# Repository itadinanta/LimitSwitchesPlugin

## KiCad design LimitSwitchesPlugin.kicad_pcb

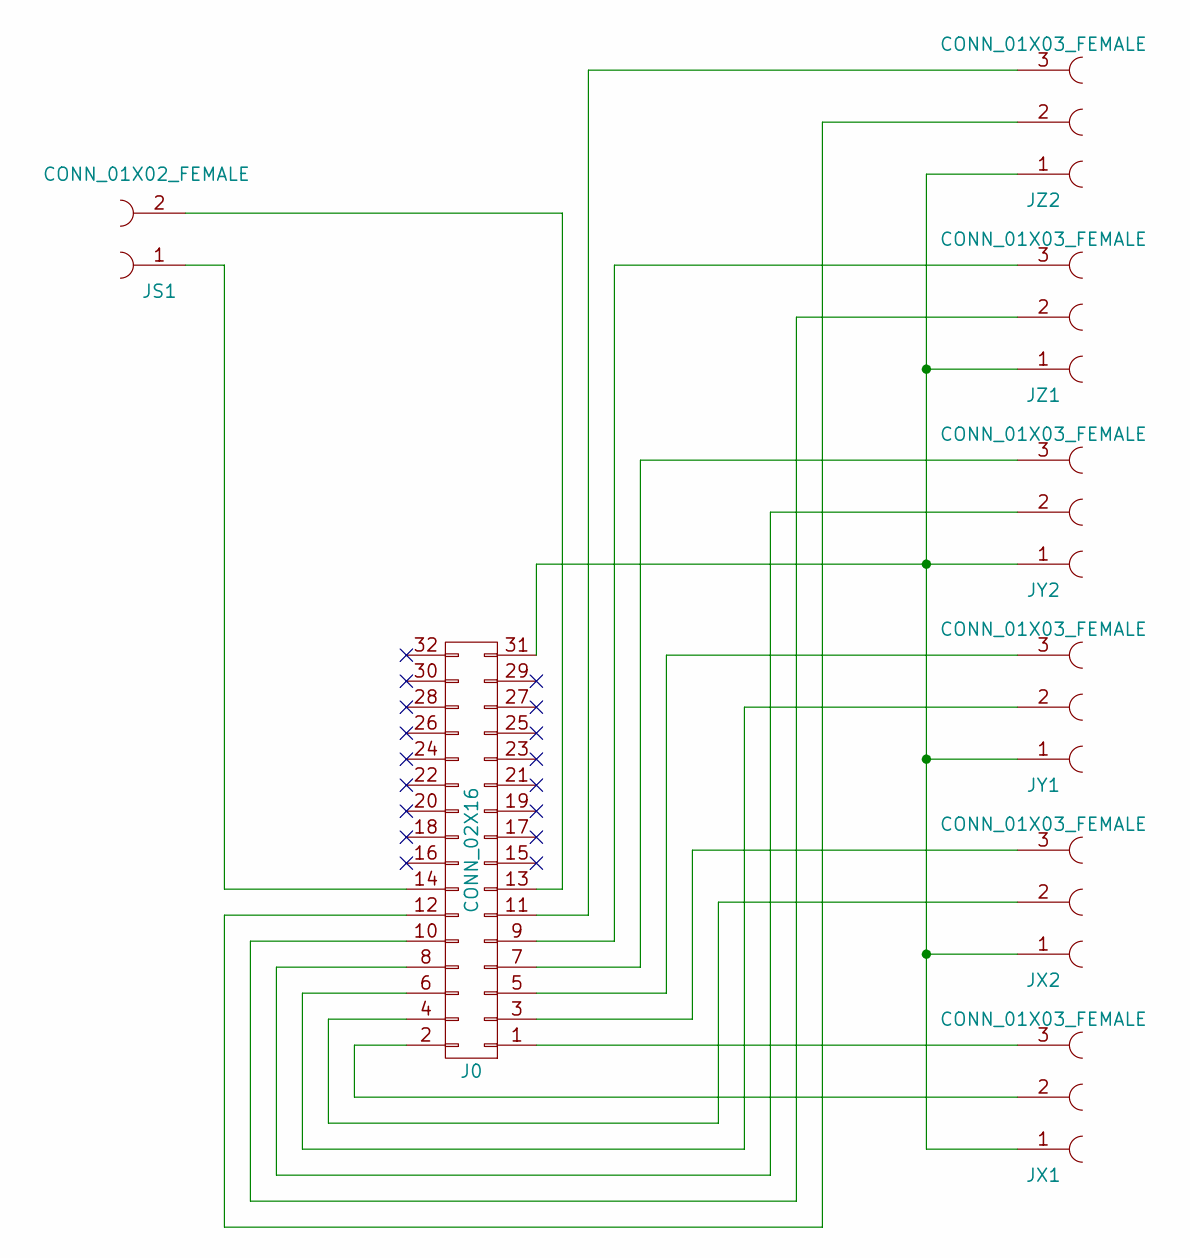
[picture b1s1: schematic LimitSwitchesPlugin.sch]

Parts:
J0: CONN_02X16; Pin_Header_Straight_2x16_Pitch2.54mm
JS1: CONN_01X02_FEMALE; JST_XH_B02B-XH-A_02x2.50mm_Straight
JX1, JX2: CONN_01X03_FEMALE; JST_XH_B03B-XH-A_03x2.50mm_Straight
JY1, JY2: CONN_01X03_FEMALE; JST_XH_B03B-XH-A_03x2.50mm_Straight
JZ1, JZ2: CONN_01X03_FEMALE; JST_XH_B03B-XH-A_03x2.50mm_Straight

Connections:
unnamed: J0.1, JX1.3
unnamed: J0.2, JX1.2
unnamed: J0.3, JX2.3
unnamed: J0.4, JX2.2
unnamed: J0.5, JY1.3
unnamed: J0.6, JY1.2
unnamed: J0.7, JY2.3
unnamed: J0.8, JY2.2
unnamed: J0.9, JZ1.3
unnamed: J0.10, JZ1.2
unnamed: J0.11, JZ2.3
unnamed: J0.12, JZ2.2
unnamed: J0.13, JS1.2
unnamed: J0.14, JS1.1
unnamed: J0.31, JX1.1, JX2.1, JY1.1, JY2.1, JZ1.1, JZ2.1

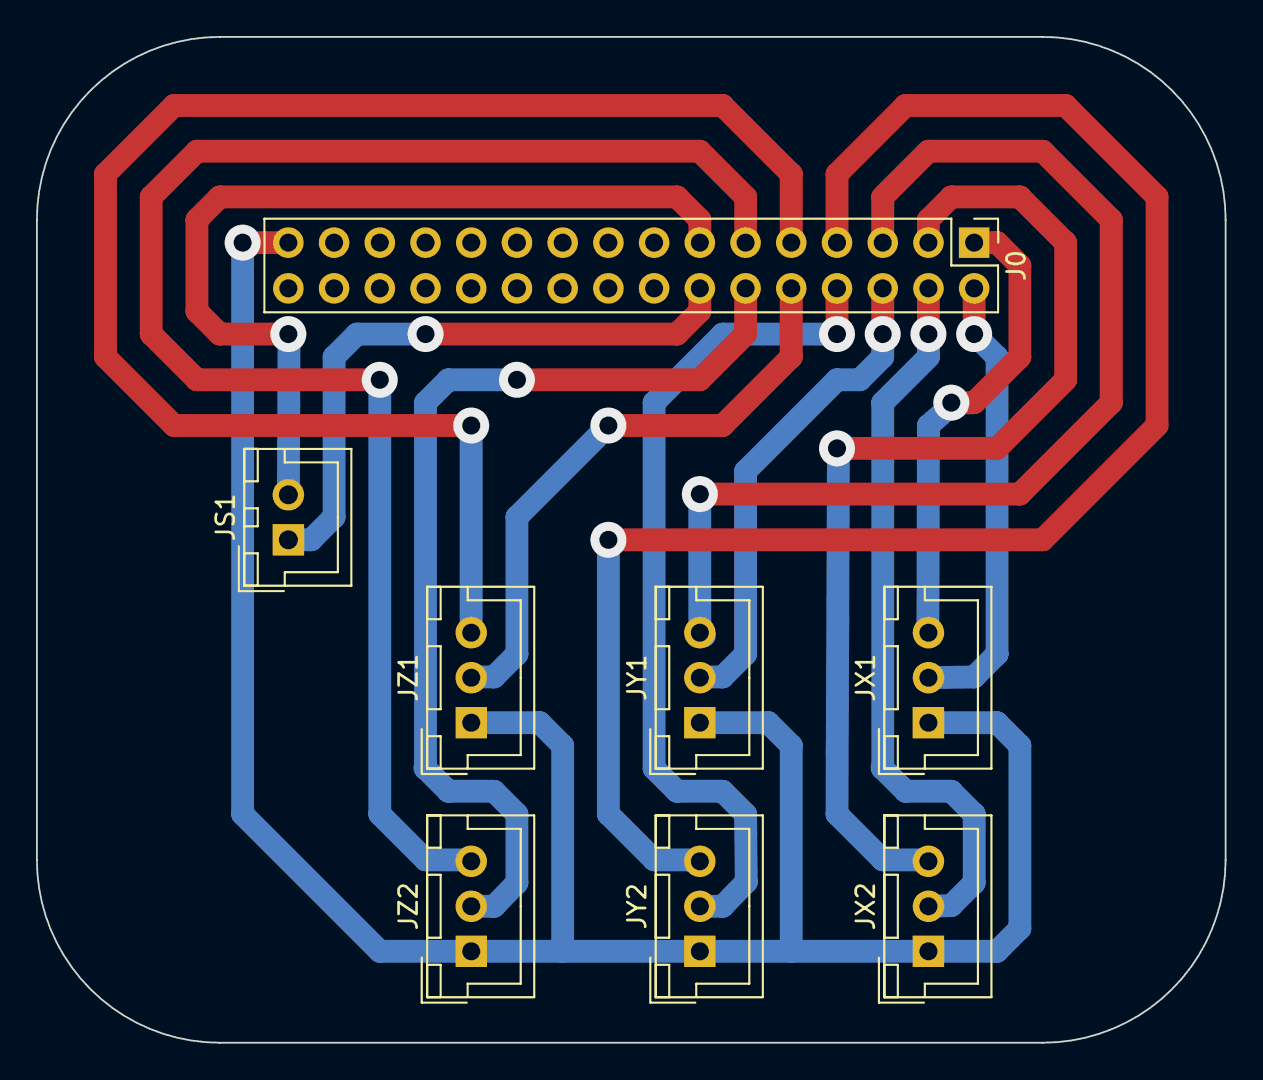
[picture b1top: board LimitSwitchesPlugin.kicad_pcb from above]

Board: 2 copper layers, 66.0 x 55.9 mm, 8 parts (0 on the bottom side), 15 nets.

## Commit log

2017-07-01 Working PCB and milling but wrong size
2017-07-02 One row layout
2017-07-03 More compact resolution
2017-07-04 Redesign of the board with all connectors beneath the pin headers
2017-07-07 New layout G-Code
2017-07-14 Pre-paint
2017-07-17 Final version with wrong number of pins
